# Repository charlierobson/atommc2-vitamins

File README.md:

# atommc2-vitamins

### Here you will find:

[The Fine Manual](https://github.com/charlierobson/atommc2-vitamins/wiki/The-Fine-Manual)
  
Some PCBs to make and enjoy
* 8k video RAM
  * Gives a full 8K of RAM at #8000, in one chip.
* Kernal + AtoMMC ROM mod
  * Frees up the extension ROM socket and the IRQ line.

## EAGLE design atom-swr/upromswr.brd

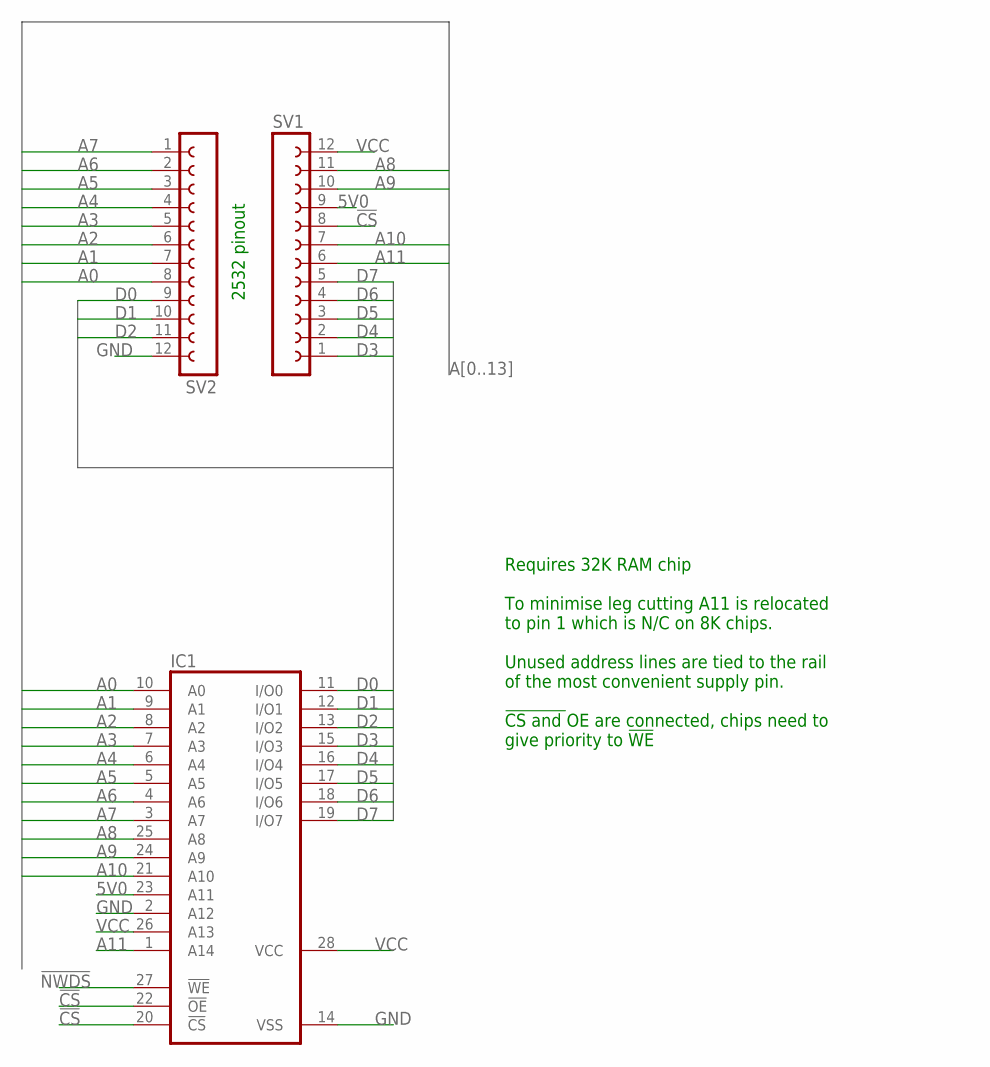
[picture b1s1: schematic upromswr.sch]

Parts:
IC1: 62256P; DIL28-6
SV1, SV2: FE12-1; FE12

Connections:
5V0: IC1.23 (A11), SV1.9
!CS: IC1.20 (!CS), IC1.22 (!OE), SV1.8
!NWDS: IC1.27 (!WE)
A0: IC1.10 (A0), SV2.8
A1: IC1.9 (A1), SV2.7
A2: IC1.8 (A2), SV2.6
A3: IC1.7 (A3), SV2.5
A4: IC1.6 (A4), SV2.4
A5: IC1.5 (A5), SV2.3
A6: IC1.4 (A6), SV2.2
A7: IC1.3 (A7), SV2.1
A8: IC1.25 (A8), SV1.11
A9: IC1.24 (A9), SV1.10
A10: IC1.21 (A10), SV1.7
A11: IC1.1 (A14), SV1.6
D0: IC1.11 (I/O0), SV2.9
D1: IC1.12 (I/O1), SV2.10
D2: IC1.13 (I/O2), SV2.11
D3: IC1.15 (I/O3), SV1.1
D4: IC1.16 (I/O4), SV1.2
D5: IC1.17 (I/O5), SV1.3
D6: IC1.18 (I/O6), SV1.4
D7: IC1.19 (I/O7), SV1.5
GND: IC1.2 (A12), IC1.14 (VSS), SV2.12
VCC: IC1.26 (A13), IC1.28 (VCC), SV1.12

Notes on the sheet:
2532 pinout
Requires 32K RAM chip To minimise leg cutting A11 is relocated to pin 1 which is N/C on 8K chips. Unused address lines are tied to the rail of the most convenient supply pin. !CS and !OE are connected, chips need to give priority to !WE

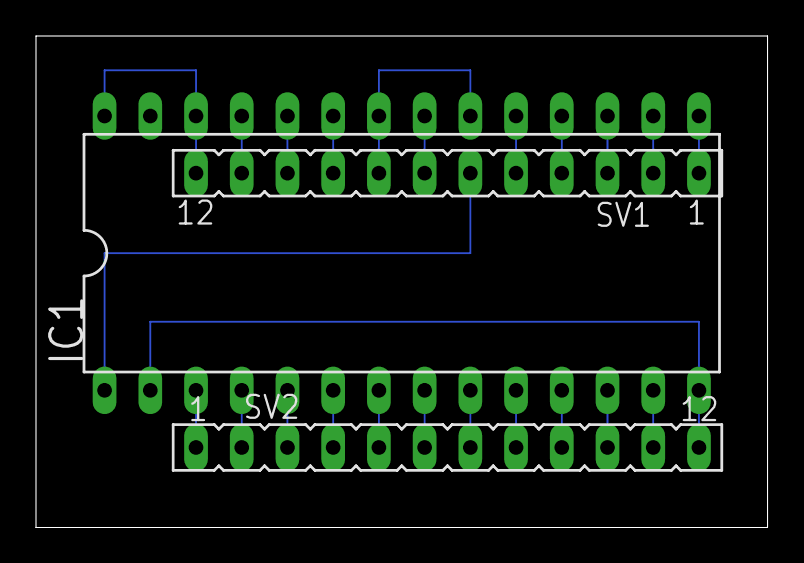
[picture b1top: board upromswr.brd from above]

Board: 2 copper layers, 40.6 x 27.3 mm, 3 parts (0 on the bottom side), 24 nets.

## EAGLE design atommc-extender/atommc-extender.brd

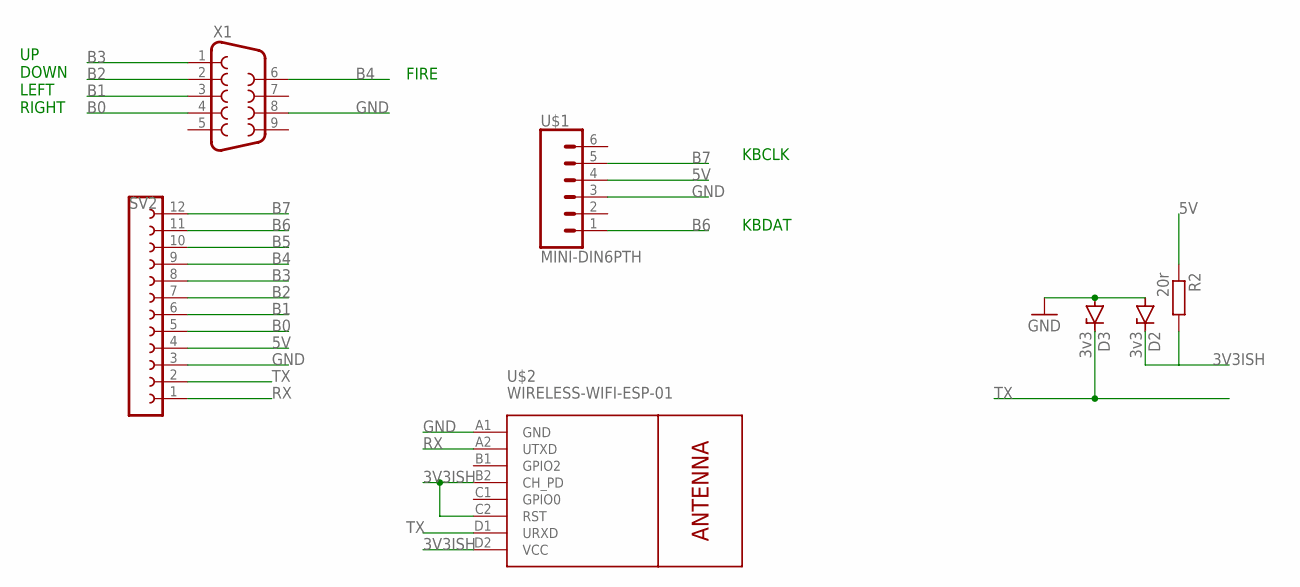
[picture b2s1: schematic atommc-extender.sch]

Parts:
D2, D3: 3v3; DO34Z7
R2: 20r; 0207/10
SV2: FE12-1; FE12
U$1: MINI-DIN6PTH; MINI-DIN6
U$2: WIRELESS-WIFI-ESP-01
X1: F09V

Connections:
3V3ISH: D2.C, R2.2, U$2.B2 (CH_PD), U$2.C2 (RST), U$2.D2 (VCC)
5V: R2.1, SV2.4, U$1.4
B0: SV2.5, X1.4
B1: SV2.6, X1.3
B2: SV2.7, X1.2
B3: SV2.8, X1.1
B4: SV2.9, X1.6
B5: SV2.10
B6: SV2.11, U$1.1
B7: SV2.12, U$1.5
GND: D2.A, D3.A, SV2.3, U$1.3, U$2.A1 (GND), X1.8
RX: SV2.1, U$2.A2 (UTXD)
TX: D3.C, SV2.2, U$2.D1 (URXD)

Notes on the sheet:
UP DOWN LEFT RIGHT
FIRE
KBCLK KBDAT

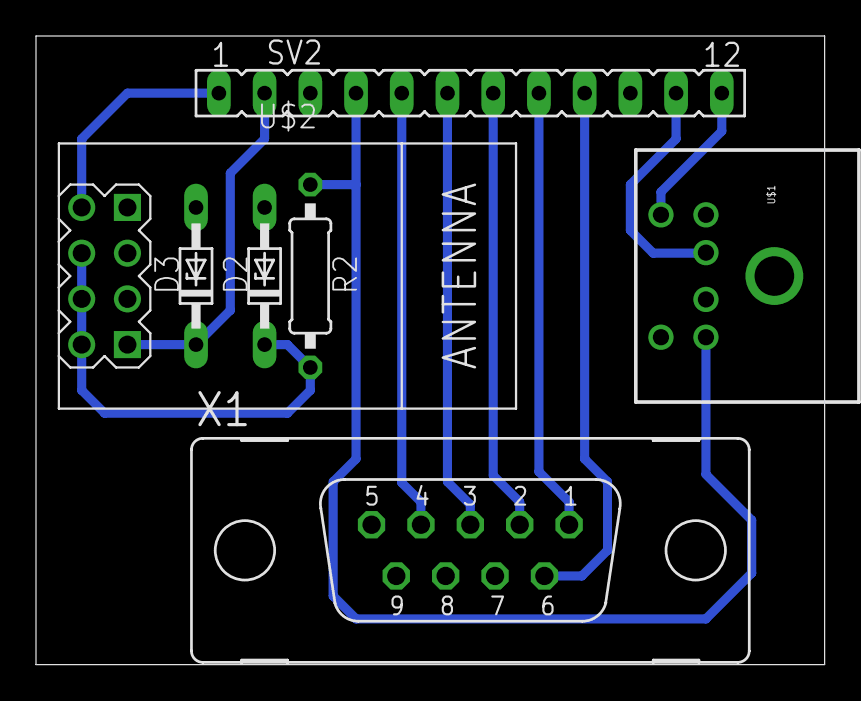
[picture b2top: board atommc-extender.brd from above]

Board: 2 copper layers, 43.8 x 34.9 mm, 7 parts (0 on the bottom side), 12 nets.

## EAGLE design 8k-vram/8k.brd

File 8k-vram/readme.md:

A re-working of this, the [C-mos (video) hooggeheuge](http://acornatom.nl/hardware/cmos/cmos.html)

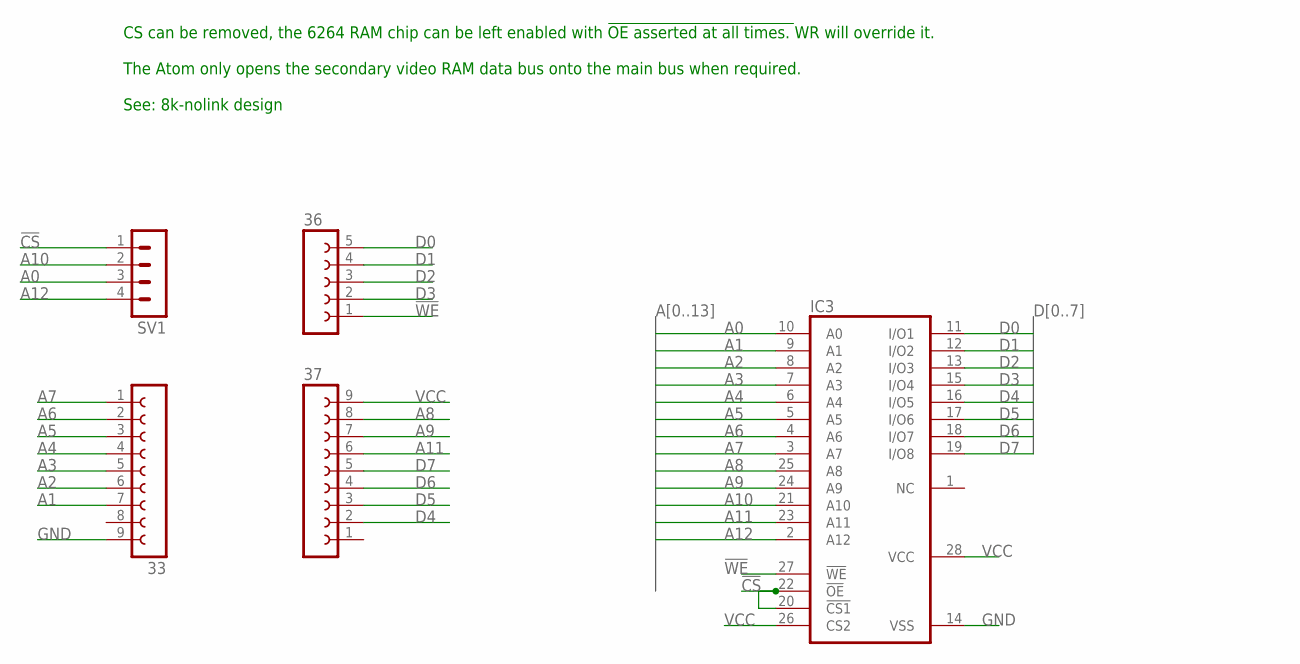
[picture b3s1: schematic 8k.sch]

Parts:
33, 37: FE09-1; FE09
36: FE05-1
IC3: 6264A; DIL28-6
SV1: MA04-1

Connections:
!CS: IC3.20 (!CS1), IC3.22 (!OE), SV1.1
!WE: 36.1, IC3.27 (!WE)
A0: IC3.10 (A0), SV1.3
A1: 33.7, IC3.9 (A1)
A2: 33.6, IC3.8 (A2)
A3: 33.5, IC3.7 (A3)
A4: 33.4, IC3.6 (A4)
A5: 33.3, IC3.5 (A5)
A6: 33.2, IC3.4 (A6)
A7: 33.1, IC3.3 (A7)
A8: 37.8, IC3.25 (A8)
A9: 37.7, IC3.24 (A9)
A10: IC3.21 (A10), SV1.2
A11: 37.6, IC3.23 (A11)
A12: IC3.2 (A12), SV1.4
D0: 36.5, IC3.11 (I/O1)
D1: 36.4, IC3.12 (I/O2)
D2: 36.3, IC3.13 (I/O3)
D3: 36.2, IC3.15 (I/O4)
D4: 37.2, IC3.16 (I/O5)
D5: 37.3, IC3.17 (I/O6)
D6: 37.4, IC3.18 (I/O7)
D7: 37.5, IC3.19 (I/O8)
GND: 33.9, IC3.14 (VSS)
VCC: 37.9, IC3.26 (CS2), IC3.28 (VCC)

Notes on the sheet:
CS can be removed, the 6264 RAM chip can be left enabled with !OE asserted at all times. !WR will override it. The Atom only opens the secondary video RAM data bus onto the main bus when required. See: 8k-nolink design

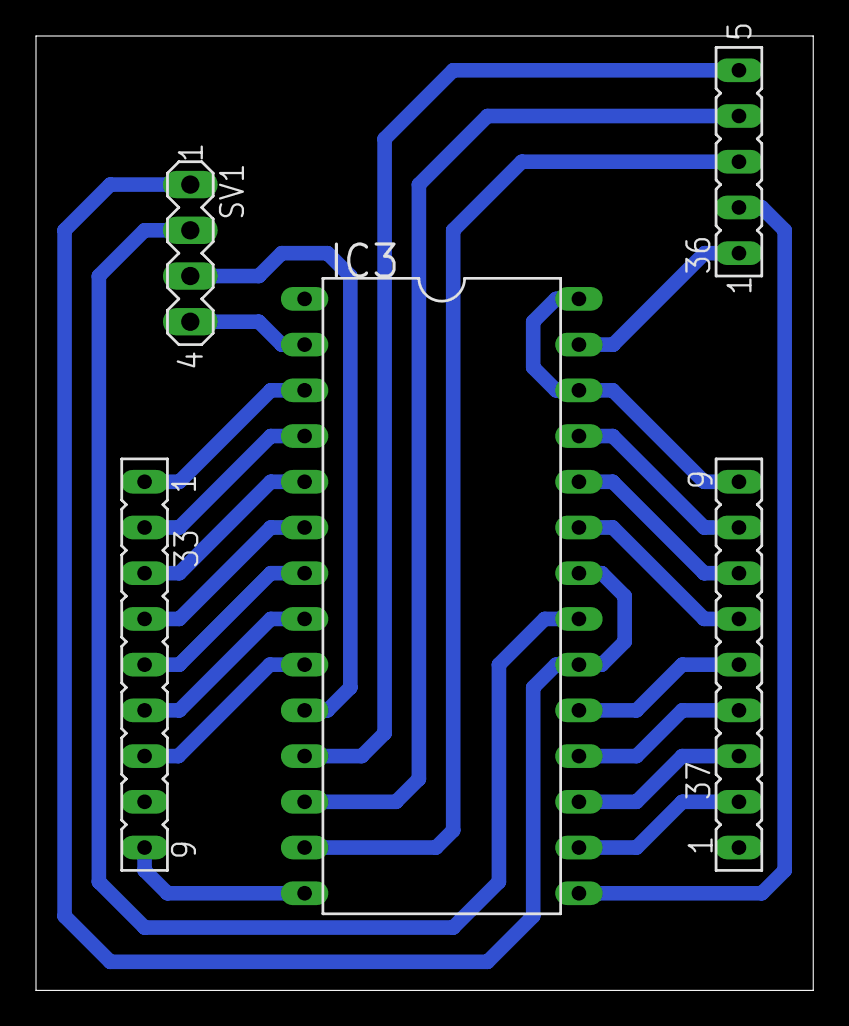
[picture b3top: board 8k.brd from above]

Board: 2 copper layers, 43.2 x 53.0 mm, 5 parts (0 on the bottom side), 25 nets.

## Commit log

2020-05-20 Adding RAM board
2020-05-20 adding uprom
2020-05-22 adding swr
2020-06-01 adding extender and swr notes

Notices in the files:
parts and their libraries:
SparkFun-Retired: Licensing: Creative Commons ShareAlike 4.0 International - https://creativecommons.org/licenses/by-sa/4.0
diy-modules: Released under the Creative Commons Attribution 4.0 International License: http://creativecommons.org/licenses/by/4.0
